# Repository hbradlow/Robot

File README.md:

Robot
=====

A small critter so I can learn PCB.

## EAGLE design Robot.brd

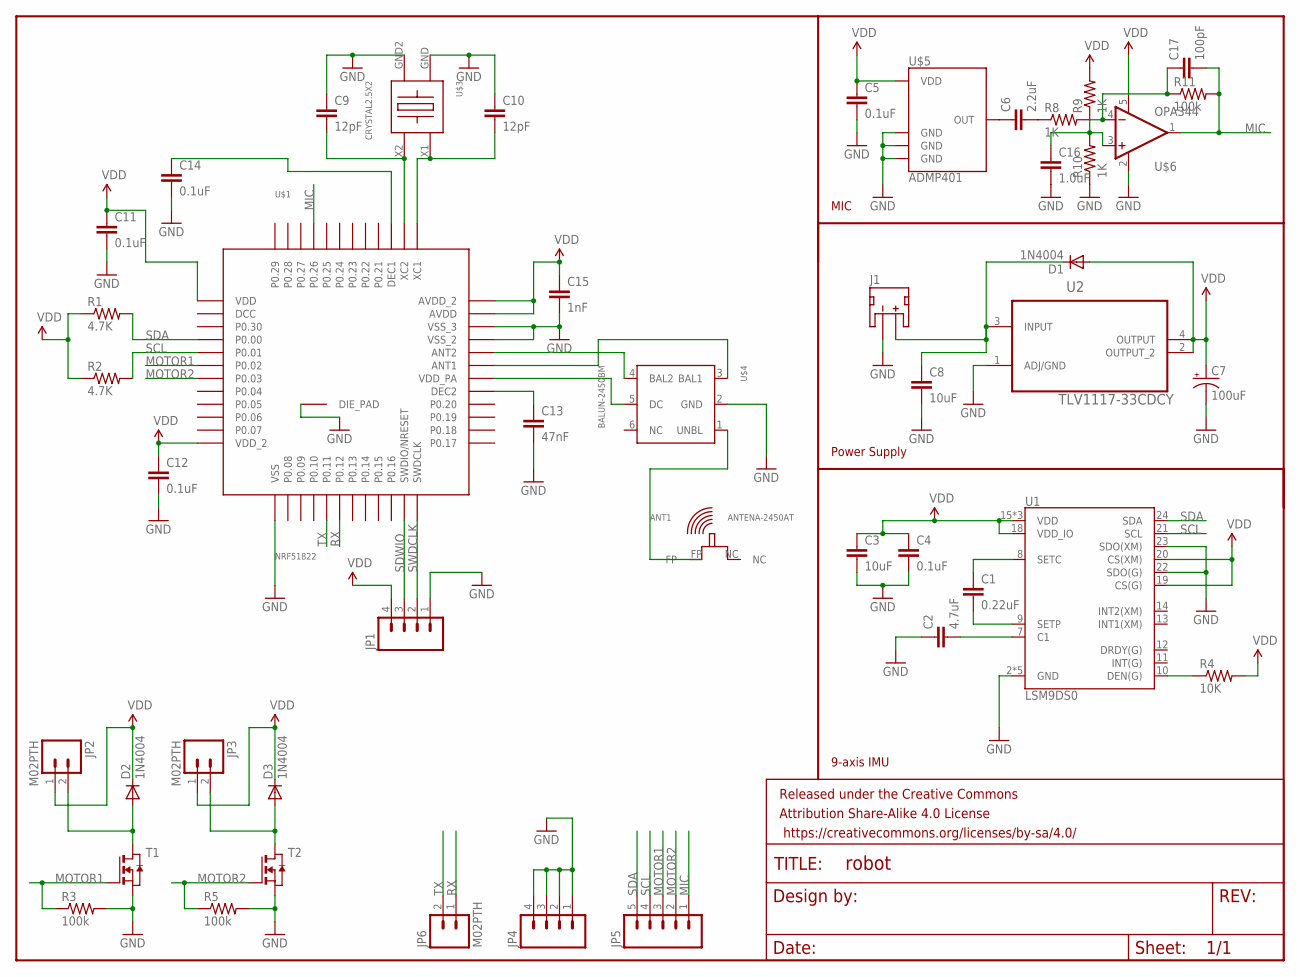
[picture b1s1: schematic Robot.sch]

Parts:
ANT1: ANTENA-2450AT; 2450AT18B100
C1: 0.22uF; 0603-CAP
C2: 4.7uF; 0603-CAP
C3, C8: 10uF; 0603-CAP
C4, C5, C11, C12, C14: 0.1uF; 0603-CAP
C6: 2.2uF; 0603-CAP
C7: 100uF; EIA7343
C9, C10: 12pF; 0603-CAP
C13: 47nF; 0603-CAP
C15: 1nF; 0603-CAP
C16: 1.0uF; 0603-CAP
C17: 100pF; 0603-CAP
D1, D2, D3: 1N4004; DO41-10
FRAME1: FRAME-LETTER; CREATIVE_COMMONS
J1: JST_2MM_MALE; JST-2-SMD
JP1, JP4: M04PTH; 1X04
JP2, JP3, JP6: M02PTH; 1X02
JP5: M05PTH; 1X05
R1, R2: 4.7K; 0603-RES
R3, R5, R11: 100k; 0603-RES
R4: 10K; 0603-RES
R8, R9, R10: 1K; 0603-RES
T1, T2: NMOSSOT23; SOT-23
U1: LSM9DS0; LGA-24
U2: TLV1117-33CDCY; SOT230P700X180-4N
U$1: NRF51822; QFN48
U$3: CRYSTAL2.5X2; 2.5X2MM
U$4: BALUN-2450BM; 2450BM14A0002
U$5: ADMP401
U$6: OPA344; SOT23-5

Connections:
GND: C2.1, C3.2, C4.2, C5.2, C7.C (-), C8.2, C9.1, C10.1, C11.2, C12.2, C13.2, C14.2, C15.2, C16.2, J1.1 (-), JP1.1, JP4.1, JP4.2, JP4.3, JP4.4, R3.2, R5.2, R10.1, T1.2 (S), T2.2 (S), U1.2 (GND), U1.3 (GND), U1.4 (GND), U1.5 (GND), U1.6 (GND), U1.22 (SDO(G)), U1.23 (SDO(XM)), U2.1 (ADJ/GND), U$1.13 (VSS), U$1.33 (VSS_2), U$1.34 (VSS_3), U$1.GND (DIE_PAD), U$3.GND, U$3.GND2, U$4.2 (GND), U$5.2 (GND), U$5.4 (GND), U$5.6 (GND), U$6.2 (V-)
MIC: C17.2, JP5.1, R11.2, U$1.45 (P0.26), U$6.1 (OUT)
MOTOR1: JP5.3, R3.1, T1.3 (G), U$1.6 (P0.02)
MOTOR2: JP5.2, R5.1, T2.3 (G), U$1.7 (P0.03)
unnamed: C1.1, U1.8 (SETC)
unnamed: C1.2, U1.9 (SETP)
unnamed: C2.2, U1.7 (C1)
unnamed: R4.1, U1.10 (DEN(G))
unnamed: C8.1, D1.C, J1.2 (+), U2.3 (INPUT)
unnamed: C6.1, U$5.1 (OUT)
unnamed: C13.1, U$1.29 (DEC2)
unnamed: C9.2, U$1.38 (XC2), U$3.X2
unnamed: C10.2, U$1.37 (XC1), U$3.X1
unnamed: C14.1, U$1.39 (DEC1)
unnamed: U$1.32 (ANT2), U$4.4 (BAL2)
unnamed: U$1.31 (ANT1), U$4.3 (BAL1)
unnamed: U$1.30 (VDD_PA), U$4.5 (DC)
unnamed: ANT1.FP, U$4.1 (UNBL)
unnamed: D2.A, JP2.2, T1.1 (D)
unnamed: D3.A, JP3.2, T2.1 (D)
unnamed: C6.2, R8.1
unnamed: C16.1, R9.1, R10.2, U$6.3 (+IN)
unnamed: C17.1, R8.2, R11.1, U$6.4 (-IN)
RX: JP6.1, U$1.18 (P0.12)
SCL: JP5.4, R2.2, U1.21 (SCL), U$1.5 (P0.01)
SDA: JP5.5, R1.2, U1.24 (SDA), U$1.4 (P0.00)
SDWIO: JP1.3, U$1.23 (SWDIO/NRESET)
SWDCLK: JP1.2, U$1.24 (SWDCLK)
TX: JP6.2, U$1.17 (P0.11)
VDD: C3.1, C4.1, C5.1, C7.A (+), C11.1, C12.1, C15.1, D1.A, D2.C, D3.C, JP1.4, JP2.1, JP3.1, R1.1, R2.1, R4.2, R9.2, U1.15 (VDD), U1.16 (VDD), U1.17 (VDD), U1.18 (VDD_IO), U1.19 (CS(G)), U1.20 (CS(XM)), U2.2 (OUTPUT_2), U2.4 (OUTPUT), U$1.1 (VDD), U$1.12 (VDD_2), U$1.35 (AVDD), U$1.36 (AVDD_2), U$5.5 (VDD), U$6.5 (V+)

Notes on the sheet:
9-axis IMU
Power Supply
MIC

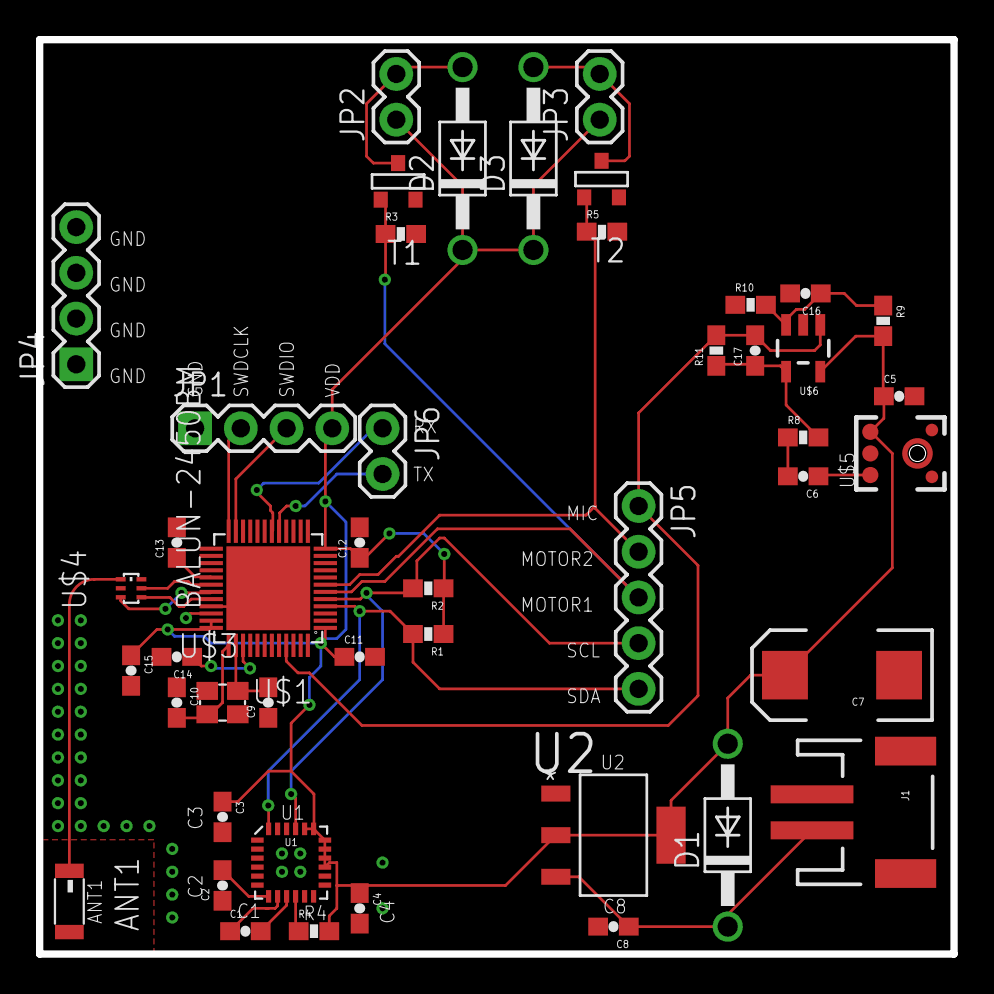
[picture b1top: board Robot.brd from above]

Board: 2 copper layers, 50.8 x 50.8 mm, 47 parts (0 on the bottom side), 30 nets.

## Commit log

2014-12-01 Adding beginning of schematic
2014-12-01 Almost done with LSM9DS0
2014-12-01 did some routing
2014-12-01 fixed routing problem
2014-12-04 ALmost done with layout
2014-12-04 Finished layout
2014-12-08 Working on silk screen

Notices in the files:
parts and their libraries:
SparkFun-Capacitors: Licensing: Creative Commons ShareAlike 4.0 International - https://creativecommons.org/licenses/by-sa/4.0
SparkFun-Aesthetics: Released under the Creative Commons Attribution Share-Alike 4.0 License
SparkFun-Aesthetics: https://creativecommons.org/licenses/by-sa/4.0
